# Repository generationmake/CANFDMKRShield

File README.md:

# CANFDMKRShield
Shield with CAN FD Controller MCP2517 for Arduino MKR

## pin usage

### Arduino MKR connector CN1

| **Pin** | **Pin Name** | **Signal**    | **Description**                      |
|:-------:|:------------:|:-------------:|:------------------------------------:|
| 1       | AREF         |               |                                      |
| 2       | DAC0/A0      |               |                                      |
| 3       | A1           |               |                                      |
| 4       | A2           |               |                                      |
| 5       | A3           |               |                                      |
| 6       | A4           |               |                                      |
| 7       | A5           |               |                                      |
| 8       | A6           |               |                                      |
| 9       | 0            |               |                                      |
| 10      | 1            |               |                                      |
| 11      | 2            |               |                                      |
| 12      | 3            | MCP2517_CS1   | option 1 for chip select for MCP2517 |
| 13      | 4            | MCP2517_CS2   | option 2 for chip select for MCP2517 |
| 14      | 5            |               |                                      |
| 15      | 6            |               |                                      |
| 16      | 7            | MCP2517_INT   | interrupt from MCP2517               |
| 17      | 8/MOSI       | SPI_MOSI      | SPI to MCP2517                       |
| 18      | 9/SCK        | SPI_SCK       | SPI to MCP2517                       |
| 19      | 10/MISO      | SPI_MISO      | SPI to MCP2517                       |
| 20      | 11/SDA       |               |                                      |
| 21      | 12/SCL       |               |                                      |
| 22      | 13/RX        |               |                                      |
| 23      | 14/TX        |               |                                      |
| 24      | RESET        |               |                                      |
| 25      | GND          | GND           |                                      |
| 26      | VCC          | 3V3-rail      | supply voltage for board             |
| 27      | VIN          | +5V           | 5V supply output from CAN connector  |
| 28      | 5V0          |               |                                      |

### CAN connector CN2

compatible to Sparkfun Qwiic. JST SH 1mm 4-pin.

| **Pin** | **Signal**    | **Description**                  |
|:-------:|:-------------:|:--------------------------------:|
| 1       | GND           |                                  |
| 2       | CAN_L         |                                  |
| 3       | CAN_H         |                                  |
| 4       | VCC           | input to Arduino, up to 24 V     |

### UAVCAN dronecode connector CN3 and CN4

compatible to UAVCAN dronecode. JST GH 1.25mm 4-pin.

| **Pin** | **Signal**    | **Description**                  |
|:-------:|:-------------:|:--------------------------------:|
| 1       | CANVCC        | up to 5.5 V                      |
| 2       | CAN_H         |                                  |
| 3       | CAN_L         |                                  |
| 4       | GND           |                                  |

CANVCC can be connected to Arduino via diode D2 as desribed in the dronecode spec. The direction of the diode defines wether current is sourced from the connector or supplied into the UAVCAN system. If no connection is desired just leave D2 unpopulated.

## PCB

### Top

### Bottom

## Resources

### Datasheets

 * http://ww1.microchip.com/downloads/en/DeviceDoc/MCP2517FD-External-CAN-FD-Controller-with-SPI-Interface-20005688B.pdf
 
### Arduino Libraries

 * tbd

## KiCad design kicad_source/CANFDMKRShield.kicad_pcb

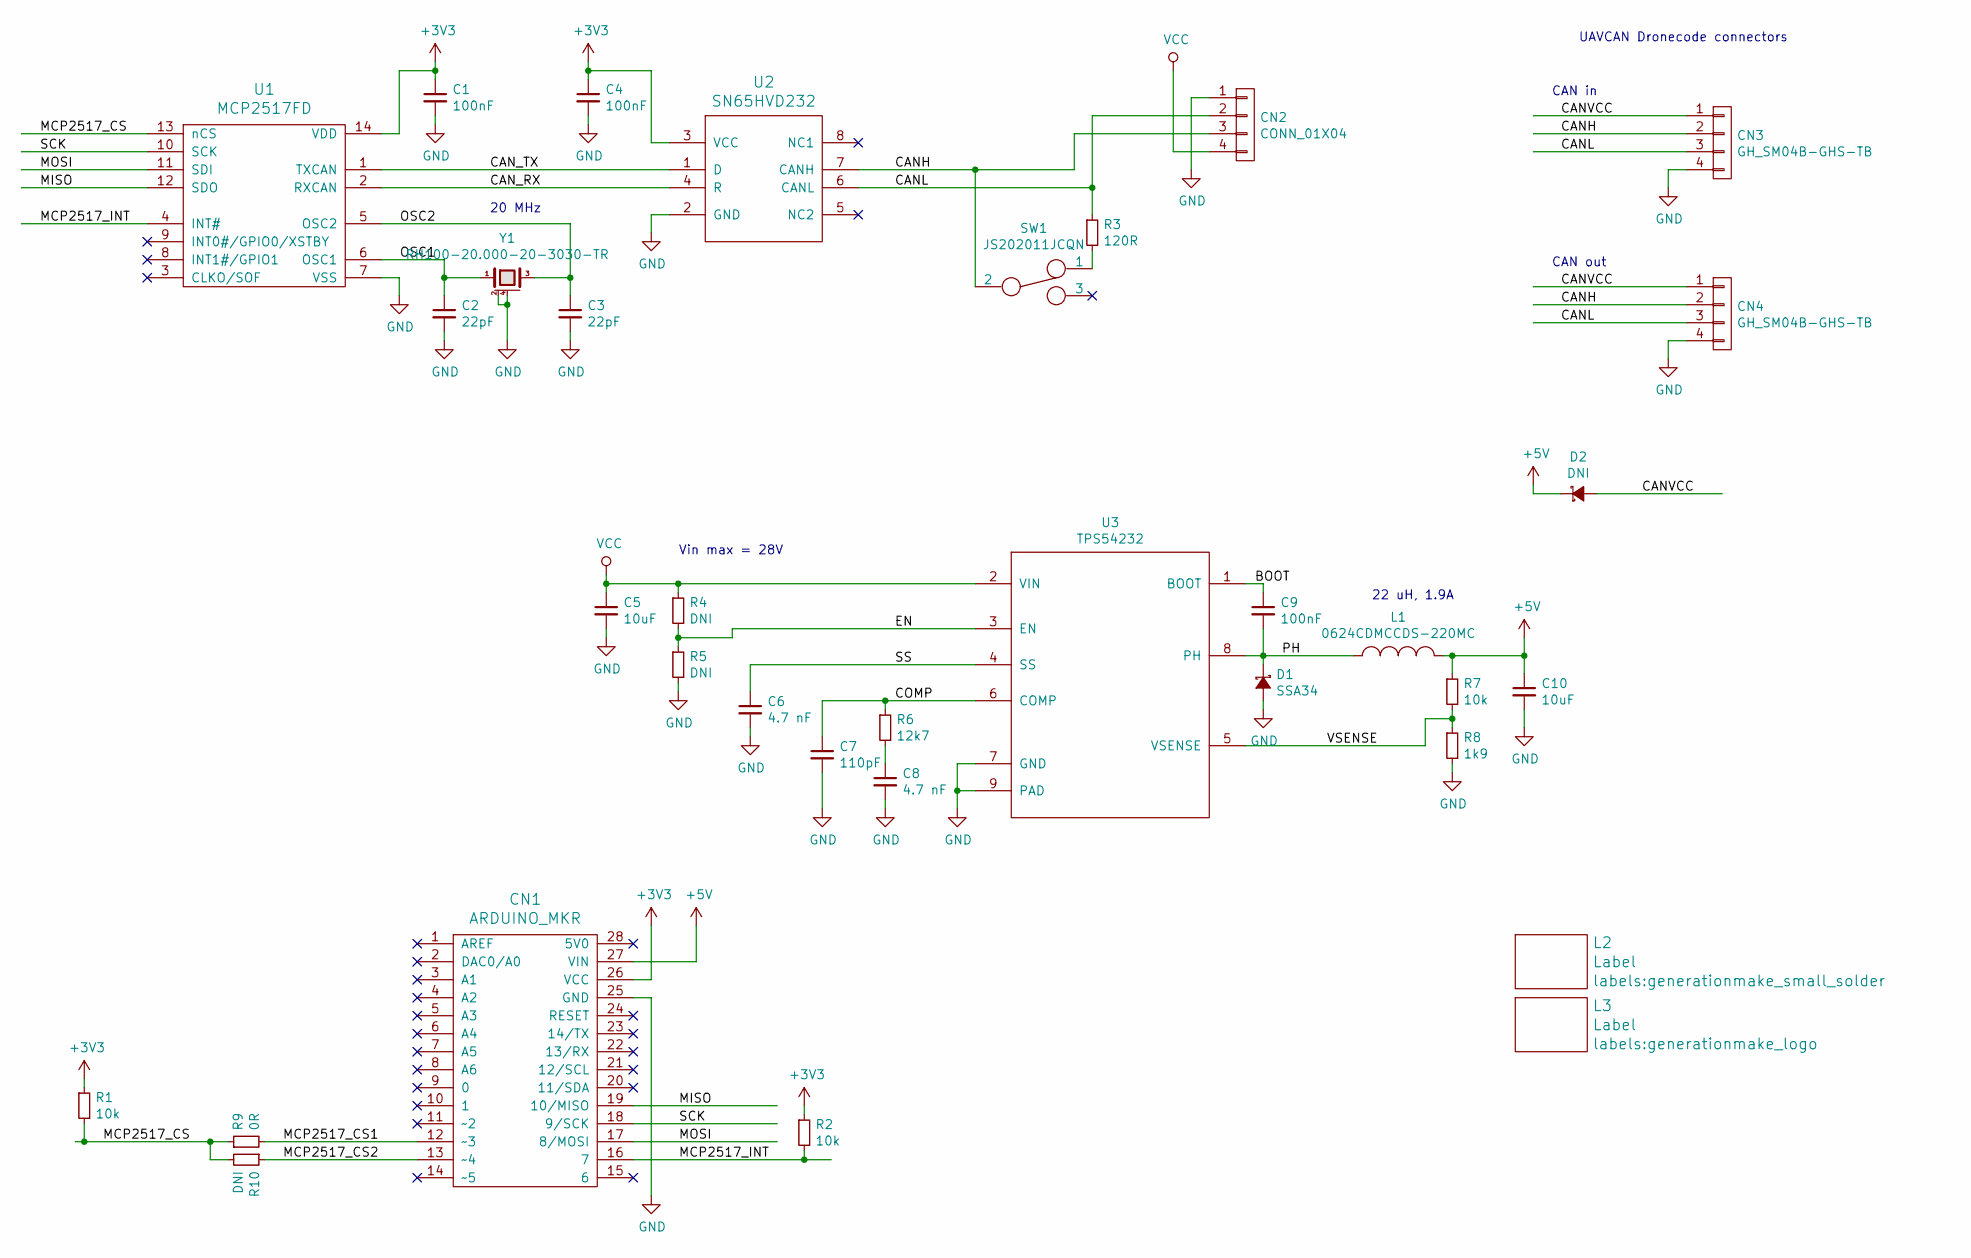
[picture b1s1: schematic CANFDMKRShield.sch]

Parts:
C1, C4, C9: 100nF; C_0603
C2, C3: 22pF; C_0603
C5, C10: 10uF; C_0805
C6, C8: 4.7 nF; C_0603
C7: 110pF; C_0603
CN1: ARDUINO_MKR; ARDUINO_MKR_HOLES_PINHEADER_EDGE
CN2: CONN_01X04; WR-TBL_691210910004
CN3, CN4: GH_SM04B-GHS-TB; JST_GH_SM04B-GHS-TB_1x04-1MP_P1.25mm_Horizontal
D1: SSA34; SMA_Standard
D2: DNI; SOD-123
L1: 0624CDMCCDS-220MC; Sumida-0624CDMCCDS
L2: Label; generationmake_small_solder
L3: Label; generationmake_logo
R1, R2, R7: 10k; R_0603
R3: 120R; R_0603
R4, R5, R10: DNI; R_0603
R6: 12k7; R_0603
R8: 1k9; R_0603
R9: 0R; R_0603
SW1: JS202011JCQN; CK_JS202011JCQN
U1: MCP2517FD; SOIC-14_3.9x8.7mm_Pitch1.27mm
U2: SN65HVD232; SOIJ-8_5.3x5.3mm_Pitch1.27mm
U3: TPS54232; SOIC-8-1EP_3.9x4.9mm_Pitch1.27mm
Y1: RH100-20.000-20-3030-TR; Crystal_SMD_3.2x2.5mm_4Pad

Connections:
+3V3: C1.1, C4.1, CN1.26 (VCC), R1.1, R2.1, U1.14 (VDD), U2.3 (VCC)
+5V: C10.1, CN1.27 (VIN), D2.1 (K), L1.2, R7.1
/BOOT: C9.1, U3.1 (BOOT)
/CANH: CN2.3, CN3.2, CN4.2, SW1.2, U2.7 (CANH)
/CANL: CN2.2, CN3.3, CN4.3, R3.1, U2.6 (CANL)
/CANVCC: CN3.1, CN4.1, D2.2 (A)
/CAN_RX: U1.2 (RXCAN), U2.4 (R)
/CAN_TX: U1.1 (TXCAN), U2.1 (D)
/COMP: C7.1, R6.1, U3.6 (COMP)
/EN: R4.2, R5.1, U3.3 (EN)
/MCP2517_CS: R1.2, R9.1, R10.2, U1.13 (nCS)
/MCP2517_CS1: CN1.12 (~~3), R9.2
/MCP2517_CS2: CN1.13 (~~4), R10.1
/MCP2517_INT: CN1.16 (7), R2.2, U1.4 (INT#)
/MISO: CN1.19 (10/MISO), U1.12 (SDO)
/MOSI: CN1.17 (8/MOSI), U1.11 (SDI)
/OSC1: C2.1, U1.6 (OSC1), Y1.1
/OSC2: C3.1, U1.5 (OSC2), Y1.3
/PH: C9.2, D1.1 (K), L1.1, U3.8 (PH)
/SCK: CN1.18 (9/SCK), U1.10 (SCK)
/SS: C6.1, U3.4 (SS)
/VSENSE: R7.2, R8.1, U3.5 (VSENSE)
GND: C1.2, C2.2, C3.2, C4.2, C5.2, C6.2, C7.2, C8.2, C10.2, CN1.25 (GND), CN2.1, CN3.4, CN4.4, D1.2 (A), R5.2, R8.2, U1.7 (VSS), U2.2 (GND), U3.7 (GND), U3.9 (PAD), Y1.2 (case), Y1.4 (case)
unnamed: C8.1, R6.2
unnamed: R3.2, SW1.1
VCC: C5.1, CN2.4, R4.1, U3.2 (VIN)

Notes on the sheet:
22 uH, 1.9A
Vin max = 28V
CAN in
UAVCAN Dronecode connectors
CAN out
20 MHz

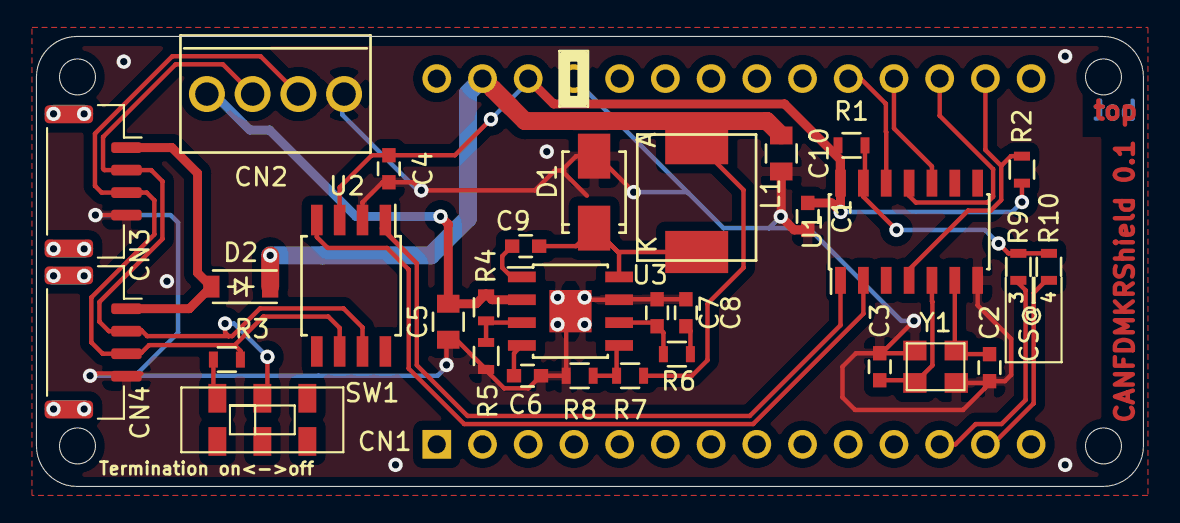
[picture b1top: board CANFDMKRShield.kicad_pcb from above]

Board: 2 copper layers, 61.5 x 25.0 mm, 34 parts (1 on the bottom side), 26 nets.

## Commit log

2020-11-15 added kicad project with schematic
2020-11-15 started layout
2020-11-15 added schematic pdf and image
2020-11-19 added voltage regulators, updated images and pdf schematic
2020-11-25 added dronecode CAN connectors, updated images and schematic pdf
2020-11-26 updated board shape, changed switch type
2020-11-27 added diode D2 to connect CAN VCC to 5V
2020-11-27 added option to use different CS line for SPI
2020-11-28 defined type of crystal, updated 3d models of footprints
2020-11-28 added pinout in readme
2020-11-28 updated layout
2020-11-28 added some labels, updated images and schematic pdf
